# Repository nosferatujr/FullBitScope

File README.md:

# FullBitScope
Power Controller and 3p Printed box for BitScope Raspberry Pi and Official Touch 7'' Display

full description in : http://nosfebloc.blogspot.com.es/

We plan also sell on line both the assembled pcb and the box, just in case you have difficulties on build yours, but first we need to buid the first working unit.

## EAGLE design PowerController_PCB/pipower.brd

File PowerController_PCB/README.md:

Schematic and PCB created with http://www.cadsoftusa.com/download-eagle/freeware/

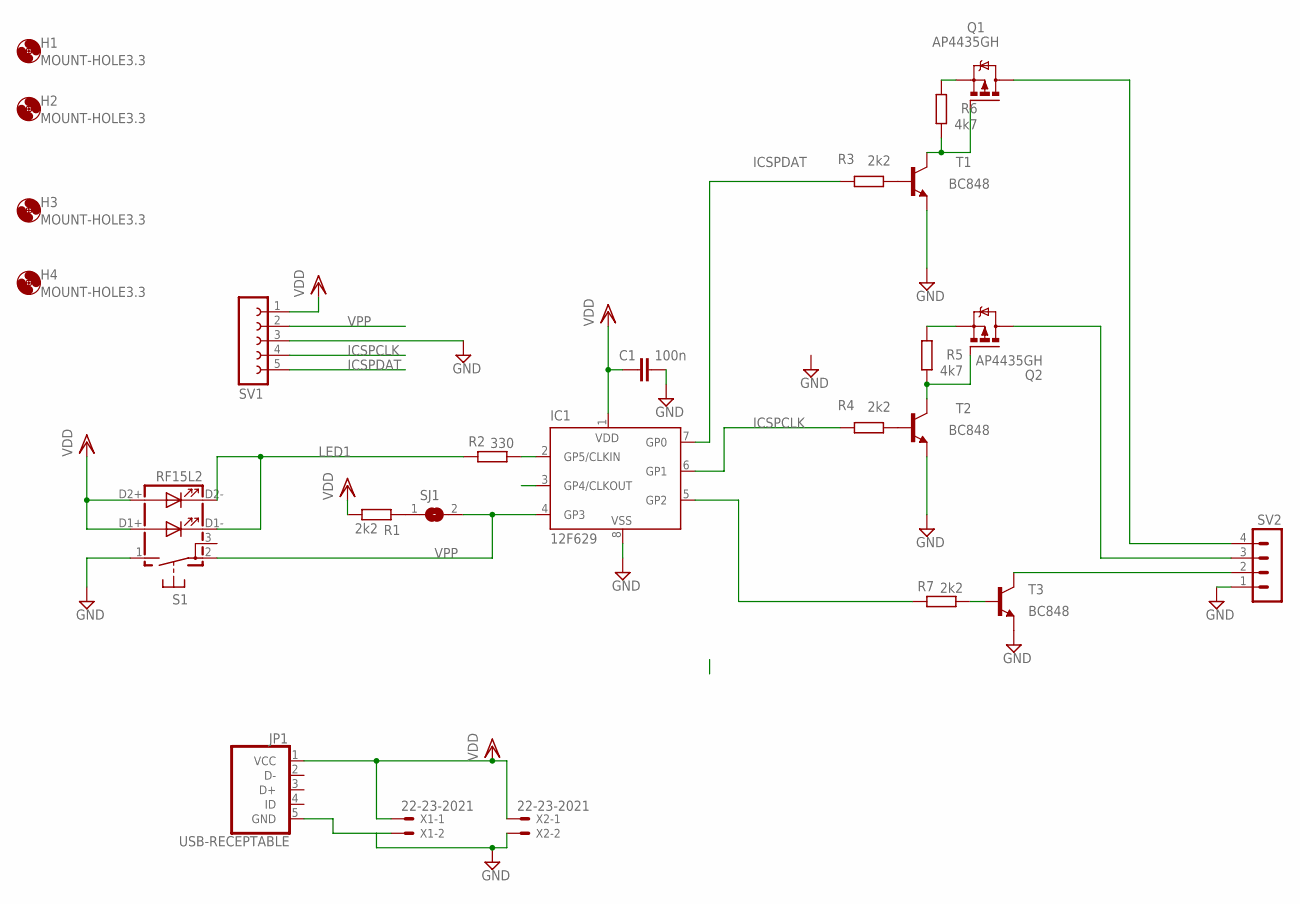
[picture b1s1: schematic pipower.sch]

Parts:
C1: 100n; C0805
H1, H2, H3, H4: MOUNT-HOLE3.3; 3,3
IC1: 12F629; SO-08; MPN PIC12F629-I/SN
JP1: USB-RECEPTABLE; FCI-10103594-0001LF
Q1, Q2: AP4435GH; D-PAK_TO252AA
R1, R3, R4, R7: 2k2; R0805
R2: 330; R0805
R5, R6: 4k7; R0805
S1: RF15L2
SJ1: SJ
SV1: FE05-1
SV2: MA04-1
T1, T2, T3: BC848; SOT23
X1, X2: 22-23-2021

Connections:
GND: C1.2, IC1.8 (VSS), JP1.5 (GND), S1.1 (S), SV1.3, SV2.1, T1.2 (E), T2.2 (E), T3.2 (E), X1.2, X2.2
ICSPCLK: IC1.6 (GP1), R4.2, SV1.4
ICSPDAT: IC1.7 (GP0), R3.2, SV1.5
LED1: R2.2, S1.D1- (C1), S1.D2- (C2)
unnamed: IC1.5 (GP2), R7.2
unnamed: Q1.4 (D), SV2.4
unnamed: Q2.1 (G), R5.1, T2.3 (C)
unnamed: Q2.3 (S), R5.2
unnamed: R3.1, T1.1 (B)
unnamed: R1.2, SJ1.1
unnamed: R4.1, T2.1 (B)
unnamed: Q2.4 (D), SV2.3
unnamed: Q1.1 (G), R6.1, T1.3 (C)
unnamed: IC1.2 (GP5/CLKIN), R2.1
unnamed: SV2.2, T3.3 (C)
unnamed: Q1.3 (S), R6.2
unnamed: R7.1, T3.1 (B)
VDD: C1.1, IC1.1 (VDD), JP1.1 (VCC), R1.1, S1.D1+ (A1), S1.D2+ (A2), SV1.1, X1.1, X2.1
VPP: IC1.4 (GP3), S1.2, SJ1.2, SV1.2

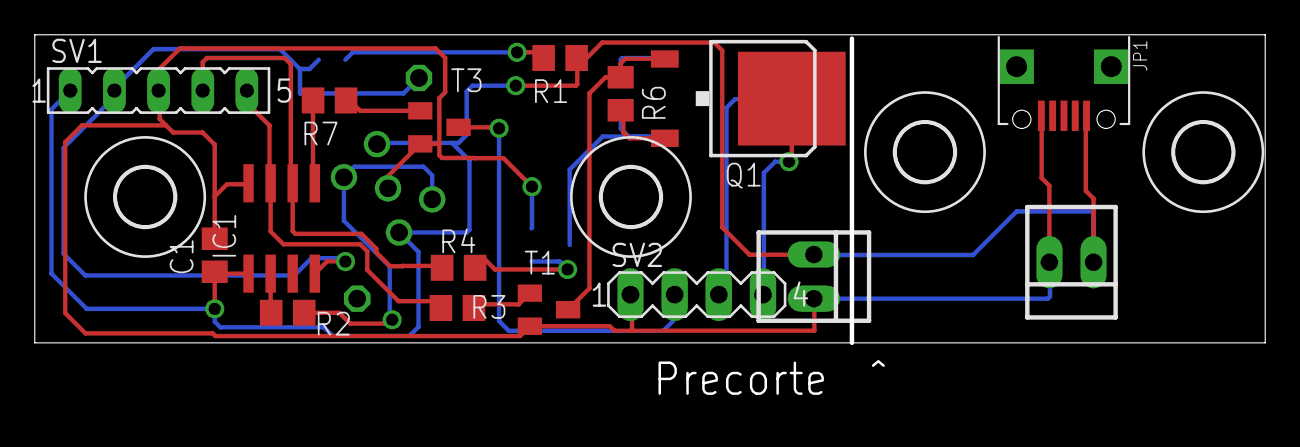
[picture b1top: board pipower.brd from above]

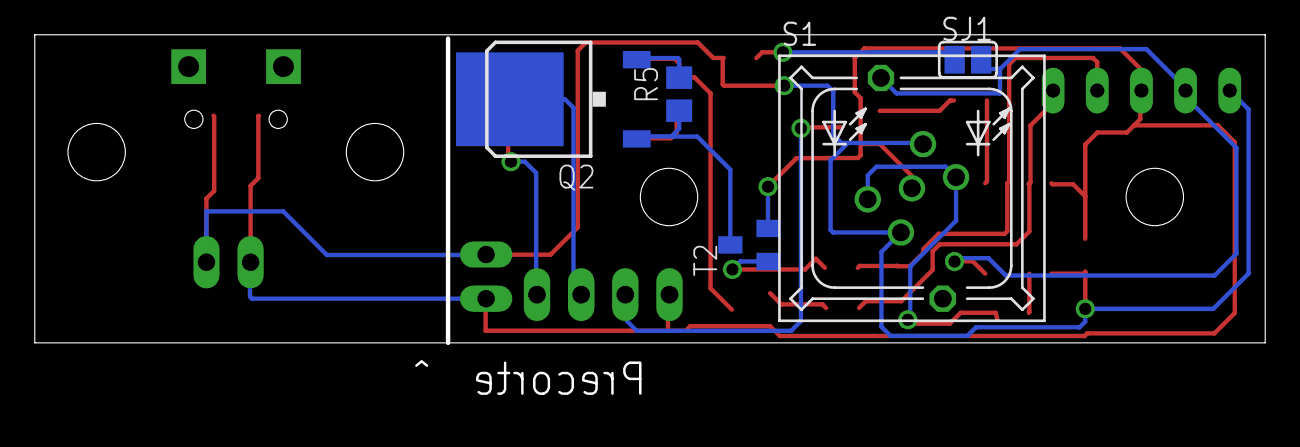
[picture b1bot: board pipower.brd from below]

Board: 2 copper layers, 70.8 x 17.7 mm, 25 parts (5 on the bottom side), 19 nets.

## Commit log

2016-02-21 :space_invader: Added .gitattributes & .gitignore files
2016-02-21 Added files via upload
2016-03-02 Files added, the hex is only for test propouses, to use on real prototipes use the one on the folder PowerController_PIC
2016-03-02 top file added
2016-03-05 full box
2016-04-21 Added files via upload
    faltaba una pista
2016-04-21 Added files via upload
    Fichero en python e instrucciones de instalacion
2016-04-21 Added files via upload
    Final production files
